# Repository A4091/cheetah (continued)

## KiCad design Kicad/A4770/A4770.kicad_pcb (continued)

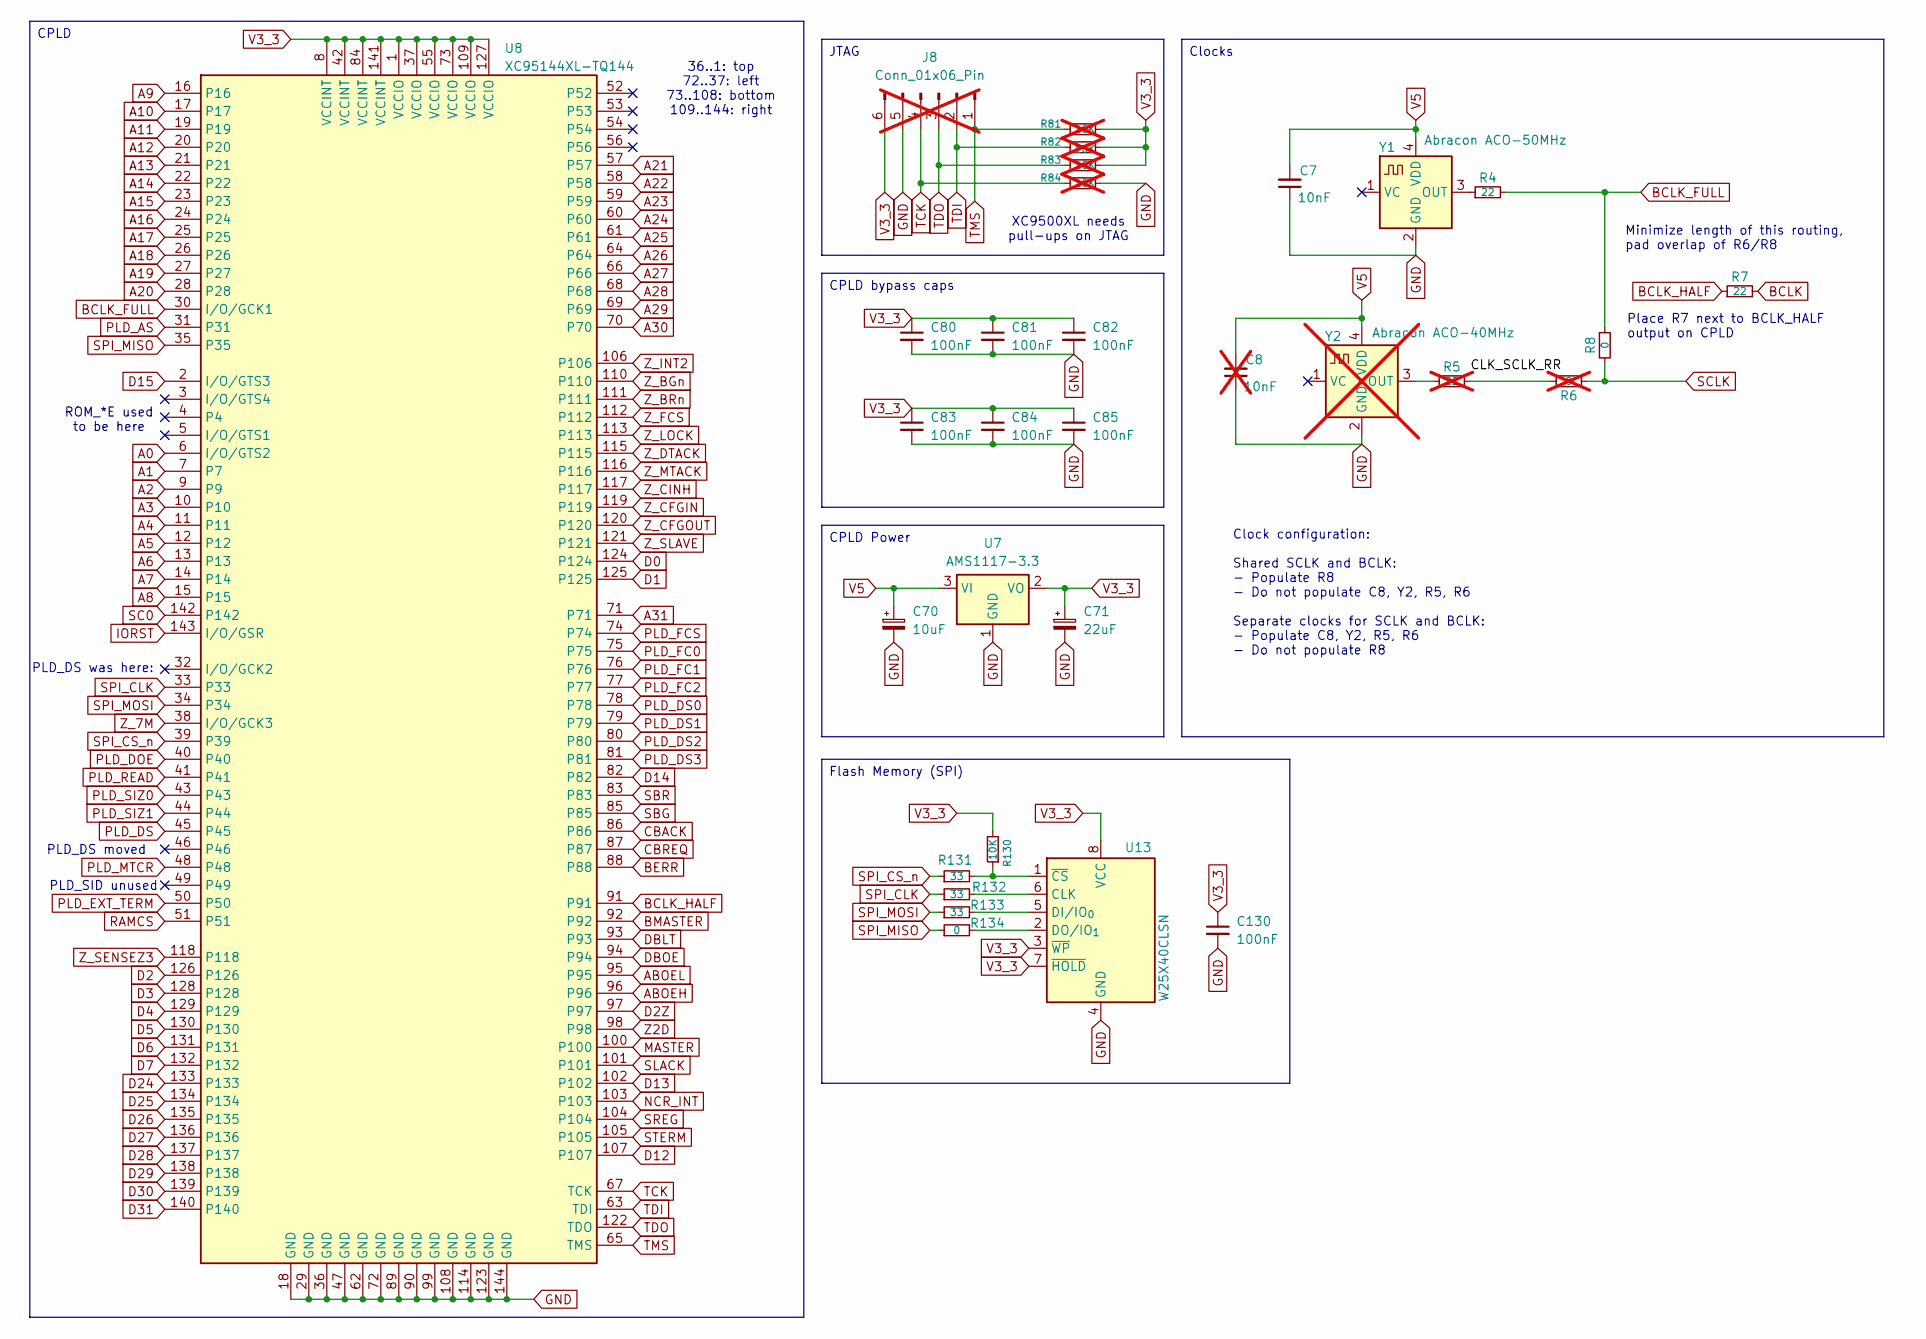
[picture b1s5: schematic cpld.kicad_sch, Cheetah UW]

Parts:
C7: 10nF; C_0603_1608Metric_Pad1.08x0.95mm_HandSolder; LCSC Part # C57112
C8: 10nF; C_0603_1608Metric_Pad1.08x0.95mm_HandSolder; LCSC Part # C57112; not fitted
C70: 10uF; CP_EIA-3528-15_AVX-H_HandSolder; LCSC Part # C7194
C71: 22uF; CP_EIA-3528-15_AVX-H_HandSolder; LCSC Part # C696813
C80, C81, C82, C83, C84, C85, C130: 100nF; C_0603_1608Metric_Pad1.08x0.95mm_HandSolder; LCSC Part # C14663
J8: Conn_01x06_Pin; PinHeader_1x06_P2.54mm_Vertical; LCSC Part # C6332199; not fitted
R4, R7: 22; R_0603_1608Metric; LCSC Part # C23345
R5: 22; R_0603_1608Metric; LCSC Part # C23345; not fitted
R6: 0; R_0603_1608Metric; LCSC Part # C21189; not fitted
R8, R134: 0; R_0603_1608Metric; LCSC Part # C21189
R81, R82, R83, R84: 10K; R_0603_1608Metric_Pad0.98x0.95mm_HandSolder; LCSC Part # C25804; not fitted
R130: 10K; R_0603_1608Metric_Pad0.98x0.95mm_HandSolder; LCSC Part # C25804
R131, R132, R133: 33; R_0603_1608Metric; LCSC Part # C23140
U7: AMS1117-3.3; SOT-223-3_TabPin2; LCSC Part # C6186
U8: XC95144XL-TQ144; TQFP-144_20x20mm_P0.5mm; LCSC Part # C1521137
U13: W25X40CLSN; SOIC-8_multi; LCSC Part # C19617
Y1: Abracon ACO-50MHz; Oscillator_SMD_Fox_FT5H_5.0x3.2mm; LCSC Part # C7431196
Y2: Abracon ACO-40MHz; Oscillator_SMD_Fox_FT5H_5.0x3.2mm; LCSC Part # C7431196; not fitted

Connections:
A0: U8.6 (I/O/GTS2); also elsewhere on the board
A1: U8.7; also elsewhere on the board
A2: U8.9; also elsewhere on the board
A3: U8.10; also elsewhere on the board
A4: U8.11; also elsewhere on the board
A5: U8.12; also elsewhere on the board
A6: U8.13; also elsewhere on the board
A7: U8.14; also elsewhere on the board
A8: U8.15; also elsewhere on the board
A9: U8.16; also elsewhere on the board
A10: U8.17; also elsewhere on the board
A11: U8.19; also elsewhere on the board
A12: U8.20; also elsewhere on the board
A13: U8.21; also elsewhere on the board
A14: U8.22; also elsewhere on the board
A15: U8.23; also elsewhere on the board
A16: U8.24; also elsewhere on the board
A17: U8.25; also elsewhere on the board
A18: U8.26; also elsewhere on the board
A19: U8.27; also elsewhere on the board
A20: U8.28; also elsewhere on the board
A21: U8.57; also elsewhere on the board
A22: U8.58; also elsewhere on the board
A23: U8.59; also elsewhere on the board
A24: U8.60; also elsewhere on the board
A25: U8.61; also elsewhere on the board
A26: U8.64; also elsewhere on the board
A27: U8.66; also elsewhere on the board
A28: U8.68; also elsewhere on the board
A29: U8.69; also elsewhere on the board
A30: U8.70; also elsewhere on the board
A31: U8.71; also elsewhere on the board
ABOEH: U8.96; also elsewhere on the board
ABOEL: U8.95; also elsewhere on the board
BCLK: R7.2; also elsewhere on the board
BCLK_FULL: R4.2, R8.1, U8.30 (I/O/GCK1)
BCLK_HALF: R7.1, U8.91
BERR: U8.88; also elsewhere on the board
BMASTER: U8.92; also elsewhere on the board
CBACK: U8.86; also elsewhere on the board
CBREQ: U8.87; also elsewhere on the board
D0: U8.124; also elsewhere on the board
D1: U8.125; also elsewhere on the board
D2: U8.126; also elsewhere on the board
D2Z: U8.97; also elsewhere on the board
D3: U8.128; also elsewhere on the board
D4: U8.129; also elsewhere on the board
D5: U8.130; also elsewhere on the board
D6: U8.131; also elsewhere on the board
D7: U8.132; also elsewhere on the board
D12: U8.107; also elsewhere on the board
D13: U8.102; also elsewhere on the board
D14: U8.82; also elsewhere on the board
D15: U8.2 (I/O/GTS3); also elsewhere on the board
D24: U8.133; also elsewhere on the board
D25: U8.134; also elsewhere on the board
D26: U8.135; also elsewhere on the board
D27: U8.136; also elsewhere on the board
D28: U8.137; also elsewhere on the board
D29: U8.138; also elsewhere on the board
D30: U8.139; also elsewhere on the board
D31: U8.140; also elsewhere on the board
DBLT: U8.93; also elsewhere on the board
DBOE: U8.94; also elsewhere on the board
GND: C7.1, C8.1, C70.2, C71.2, C80.2, C81.2, C82.2, C83.2, C84.2, C85.2, C130.2, J8.5, R84.1, U7.1 (GND), U8.18 (GND), U8.29 (GND), U8.36 (GND), U8.47 (GND), U8.62 (GND), U8.72 (GND), U8.89 (GND), U8.90 (GND), U8.99 (GND), U8.108 (GND), U8.114 (GND), U8.123 (GND), U8.144 (GND), U13.4 (GND), Y1.2 (GND), Y2.2 (GND); also elsewhere on the board
IORST: U8.143 (I/O/GSR); also elsewhere on the board
MASTER: U8.100; also elsewhere on the board
NCR_INT: U8.103; also elsewhere on the board
unnamed: R5.2, R6.2
unnamed: R132.2, U13.6 (CLK)
unnamed: R133.2, U13.5 (DI/IO_{0})
unnamed: R134.2, U13.2 (DO/IO_{1})
unnamed: R130.1, R131.2, U13.1 (~CS)
unnamed: R4.1, Y1.3 (OUT)
unnamed: R5.1, Y2.3 (OUT)
PLD_AS: U8.31; also elsewhere on the board
PLD_DOE: U8.40; also elsewhere on the board
PLD_DS: U8.45; also elsewhere on the board
PLD_DS0: U8.78; also elsewhere on the board
PLD_DS1: U8.79; also elsewhere on the board
PLD_DS2: U8.80; also elsewhere on the board
PLD_DS3: U8.81; also elsewhere on the board
PLD_EXT_TERM: U8.50; also elsewhere on the board
PLD_FC0: U8.75; also elsewhere on the board
PLD_FC1: U8.76; also elsewhere on the board
PLD_FC2: U8.77; also elsewhere on the board
PLD_FCS: U8.74; also elsewhere on the board
PLD_MTCR: U8.48; also elsewhere on the board
PLD_READ: U8.41; also elsewhere on the board
PLD_SIZ0: U8.43; also elsewhere on the board
PLD_SIZ1: U8.44; also elsewhere on the board
RAMCS: U8.51; also elsewhere on the board
SBG: U8.85; also elsewhere on the board
SBR: U8.83; also elsewhere on the board
SC0: U8.142; also elsewhere on the board
SCLK: R6.1, R8.2; also elsewhere on the board
SLACK: U8.101; also elsewhere on the board
SPI_CLK: R132.1, U8.33
SPI_CS_n: R131.1, U8.39
SPI_MISO: R134.1, U8.35
SPI_MOSI: R133.1, U8.34
SREG: U8.104; also elsewhere on the board
STERM: U8.105; also elsewhere on the board
TCK: J8.4, R84.2, U8.67 (TCK)
TDI: J8.2, R82.2, U8.63 (TDI)
TDO: J8.3, R83.2, U8.122 (TDO)
TMS: J8.1, R81.2, U8.65 (TMS)
V3_3: C71.1, C80.1, C81.1, C82.1, C83.1, C84.1, C85.1, C130.1, J8.6, R81.1, R82.1, R83.1, R130.2, U7.2 (VO), U8.1 (VCCIO), U8.8 (VCCINT), U8.37 (VCCIO), U8.42 (VCCINT), U8.55 (VCCIO), U8.73 (VCCIO), U8.84 (VCCINT), U8.109 (VCCIO), U8.127 (VCCIO), U8.141 (VCCINT), U13.3 (~WP), U13.7 (~HOLD), U13.8 (VCC); also elsewhere on the board
V5: C7.2, C8.2, C70.1, U7.3 (VI), Y1.4 (VDD), Y2.4 (VDD); also elsewhere on the board
Z2D: U8.98; also elsewhere on the board
Z_7M: U8.38 (I/O/GCK3); also elsewhere on the board
Z_BGn: U8.110; also elsewhere on the board
Z_BRn: U8.111; also elsewhere on the board
Z_CFGIN: U8.119; also elsewhere on the board
Z_CFGOUT: U8.120; also elsewhere on the board
Z_CINH: U8.117; also elsewhere on the board
Z_DTACK: U8.115; also elsewhere on the board
Z_FCS: U8.112; also elsewhere on the board
Z_INT2: U8.106; also elsewhere on the board
Z_LOCK: U8.113; also elsewhere on the board
Z_MTACK: U8.116; also elsewhere on the board
Z_SENSEZ3: U8.118; also elsewhere on the board
Z_SLAVE: U8.121; also elsewhere on the board

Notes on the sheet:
Clock configuration: Shared SCLK and BCLK: - Populate R8 - Do not populate C8, Y2, R5, R6 Separate clocks for SCLK and BCLK: - Populate C8, Y2, R5, R6 - Do not populate R8
PLD_SID unused
PLD_DS moved
ROM_*E used to be here
Minimize length of this routing, pad overlap of R6/R8
36..1: top 72..37: left 73..108: bottom 109..144: right
Place R7 next to BCLK_HALF output on CPLD
XC9500XL needs pull-ups on JTAG
PLD_DS was here:
CPLD
Clocks
JTAG
CPLD Power
CPLD bypass caps
Flash Memory (SPI)

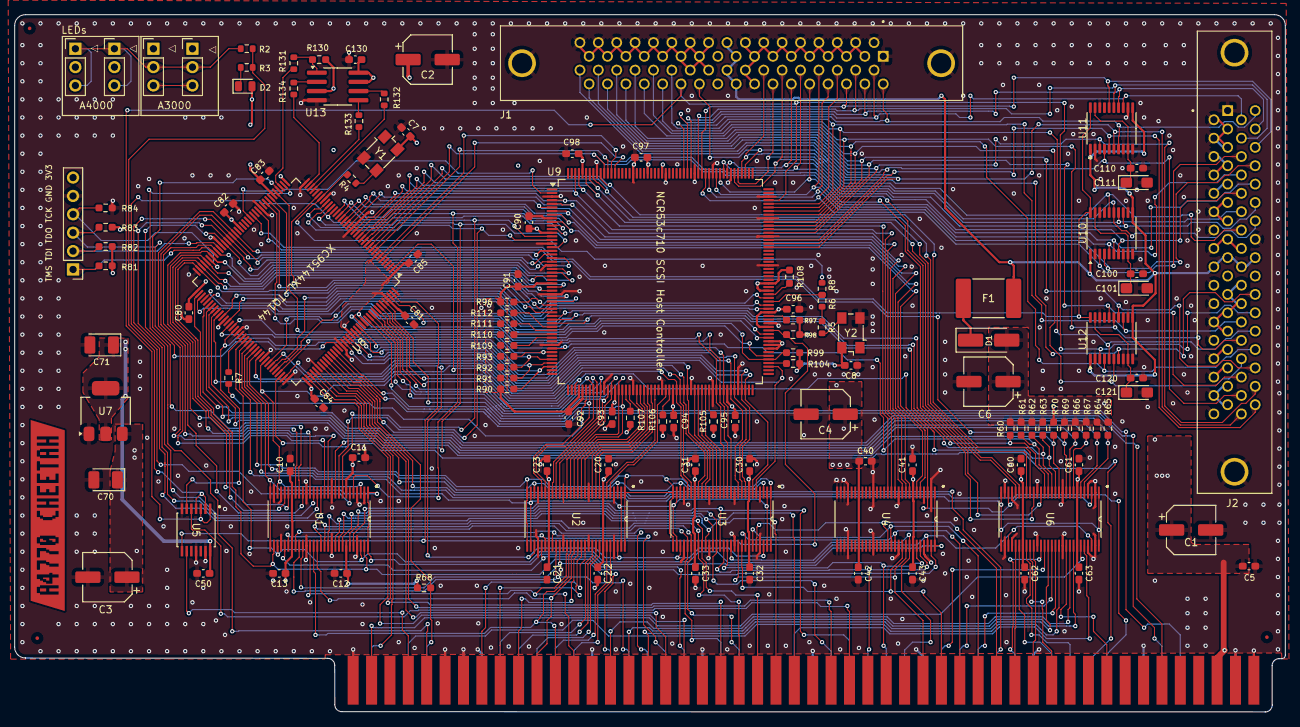
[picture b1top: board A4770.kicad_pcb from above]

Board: 4 copper layers, 175.6 x 96.4 mm, 127 parts (0 on the bottom side), 231 nets.

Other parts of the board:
kibuzzard-696E6D75: G***; kibuzzard-696E6D75

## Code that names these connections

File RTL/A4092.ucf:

# P1 - VCCIO
NET "D<15>"       LOC = "P2";
NET "D<15>"       SLEW = "SLOW";
NET "ROM_CE_n"    LOC = "P3";
NET "ROM_WE_n"    LOC = "P4";
NET "ROM_OE_n"    LOC = "P5";
NET "A<0>"        LOC = "P6";
NET "A<1>"        LOC = "P7";
# P8 - VCCINT
NET "A<2>"        LOC = "P9";
NET "A<3>"        LOC = "P10";
NET "A<4>"        LOC = "P11";
NET "A<5>"        LOC = "P12";
NET "A<6>"        LOC = "P13";
NET "A<7>"        LOC = "P14";
NET "A<8>"        LOC = "P15";
NET "A<9>"        LOC = "P16";
NET "A<10>"       LOC = "P17";
# P18 - GND
NET "A<11>"       LOC = "P19";
NET "A<12>"       LOC = "P20";
NET "A<13>"       LOC = "P21";
NET "A<14>"       LOC = "P22";
NET "A<15>"       LOC = "P23";
NET "A<16>"       LOC = "P24";
NET "A<17>"       LOC = "P25";
NET "A<18>"       LOC = "P26";
NET "A<19>"       LOC = "P27";
NET "A<20>"       LOC = "P28";
# P29 - GND
NET "CLK_50M"     LOC = "P30";
NET "CLK_50M" TNM_NET = "clk";
TIMESPEC "TS_clk" = PERIOD "clk" 20 ns HIGH 50%;
NET "SCSI_AS_n"   LOC = "P31";
NET "SCSI_DS_n"   LOC = "P32";
NET "SPI_CLK"     LOC = "P33";
NET "SPI_MOSI"    LOC = "P34";
NET "SPI_MISO"    LOC = "P35";
# P36 - GND
# P37 - VCCIO
NET "C7M"        LOC = "P38";
NET "C7M" TNM_NET = "C7M";
TIMESPEC "TS_C7M" = PERIOD "C7M" 139.68 ns HIGH 50%;
NET "SPI_CS_n"    LOC = "P39";
NET "DOE"         LOC = "P40";
NET "DOE"         SLEW = "SLOW";
NET "READ"        LOC = "P41";
NET "READ"        SLEW = "SLOW";
# P42 - VCCINT
NET "SIZ<0>"      LOC = "P43";
NET "SIZ<1>"      LOC = "P44";
# P45 - NC
# P46 - NC
# P47 - GND
NET "MTCR_n"      LOC = "P48";
NET "MTCR_n"      SLEW = "SLOW";
NET "SID_n"       LOC = "P49";
NET "DIP_EXT_TERM" LOC = "P50";
# P51 - NC
# P52 - NC
# P53 - NC
# P54 - NC
# P55 - VCCIO
# P56 - NC
# P57 - NC
# P58 - NC
NET "A<23>"       LOC = "P59";
NET "A<24>"       LOC = "P60";
NET "A<25>"       LOC = "P61";
# P62 - GND
# P63 - TDI
NET "A<26>"       LOC = "P64";
# P65 - TMS
NET "A<27>"       LOC = "P66";
# P67 - TCK
NET "A<28>"       LOC = "P68";
NET "A<29>"       LOC = "P69";
NET "A<30>"       LOC = "P70";
NET "A<31>"       LOC = "P71";
# P72 - GND
# P73 - VCCIO
NET "FCS"         LOC = "P74";
NET "FC<0>"       LOC = "P75";
NET "FC<1>"       LOC = "P76";
NET "FC<2>"       LOC = "P77";
NET "DS_n<0>"     LOC = "P78";
NET "DS_n<0>"     SLEW = "SLOW";
NET "DS_n<1>"     LOC = "P79";
NET "DS_n<1>"     SLEW = "SLOW";
NET "DS_n<2>"     LOC = "P80";
NET "DS_n<2>"     SLEW = "SLOW";
NET "DS_n<3>"     LOC = "P81";
NET "DS_n<3>"     SLEW = "SLOW";
NET "D<14>"       LOC = "P82";
NET "D<14>"       SLEW = "SLOW";
NET "SBR_n"       LOC = "P83";
# P84 - VCCINT
NET "SBG_n"       LOC = "P85";
NET "CBACK_n"     LOC = "P86";
NET "CBREQ_n"     LOC = "P87";
NET "BERR_n"      LOC = "P88";
# P89 - GND
# P90 - GND
NET "CLK"         LOC = "P91";
NET "BMASTER"     LOC = "P92";
NET "DBLT"        LOC = "P93";
NET "DBOE_n"      LOC = "P94";
NET "ABOEL_n"     LOC = "P95";
NET "ABOEH_n"     LOC = "P96";
NET "D2Z_n"       LOC = "P97";
NET "Z2D_n"       LOC = "P98";
# P99 - GND
NET "MASTER_n"    LOC = "P100";
NET "SLACK_n"     LOC = "P101";
NET "D<13>"       LOC = "P102";
NET "D<13>"       SLEW = "SLOW";
NET "SINT_n"      LOC = "P103";
NET "SCSI_SREG_n" LOC = "P104";
NET "SCSI_STERM_n" LOC = "P105";
NET "INT2_n"      LOC = "P106";
NET "INT2_n"      SLEW = "SLOW";
NET "D<12>"       LOC = "P107";
NET "D<12>"       SLEW = "SLOW";
# P108 - GND
# P109 - VCCIO
NET "BGn"         LOC = "P110";
NET "BRn"         LOC = "P111";
NET "BRn"         SLEW = "SLOW";
NET "Z_FCS_n"     LOC = "P112";
NET "Z_FCS_n"     SLEW = "SLOW";
NET "Z_LOCK"      LOC = "P113";
# P114 - GND
NET "DTACK_n"     LOC = "P115";
NET "DTACK_n"     SLEW = "SLOW";
NET "MTACK_n"     LOC = "P116";
NET "CINH_n"      LOC = "P117";
NET "CINH_n"      SLEW = "SLOW";
NET "SENSEZ3"     LOC = "P118";
NET "CFGIN_n"     LOC = "P119";
NET "CFGOUT_n"    LOC = "P120";
NET "CFGOUT_n"    SLEW = "SLOW";
NET "SLAVE_n"     LOC = "P121";
NET "SLAVE_n"     SLEW = "SLOW";
# P122 - TDO
# P123 - GND
NET "D<0>"        LOC = "P124";
NET "D<1>"        LOC = "P125";
NET "D<2>"        LOC = "P126";
# P127 - VCCIO
NET "D<3>"        LOC = "P128";
NET "D<4>"        LOC = "P129";
NET "D<5>"        LOC = "P130";
NET "D<6>"        LOC = "P131";
NET "D<7>"        LOC = "P132";
NET "D<24>"       LOC = "P133";
NET "D<25>"       LOC = "P134";
NET "D<26>"       LOC = "P135";
NET "D<27>"       LOC = "P136";
NET "D<28>"       LOC = "P137";
NET "D<28>"       SLEW = "SLOW";
NET "D<29>"       LOC = "P138";
NET "D<29>"       SLEW = "SLOW";
NET "D<30>"       LOC = "P139";
NET "D<30>"       SLEW = "SLOW";
NET "D<31>"       LOC = "P140";
NET "D<31>"       SLEW = "SLOW";
# P141 - VCCINT
NET "SC0"         LOC = "P142";
NET "IORST_n"     LOC = "P143";
NET "IORST_n" TIG;  # Ignore timing on async reset
# P144 - GND

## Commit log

2025-07-14 Fixup address decodes
    *_region was matching when slave_cycle was true but without checking that the base address matched - this would cause these regions to match when other Z3 boards are being accessed
2025-07-14 Fixup DOE
    It must be an inout not an output
    Also add a synchronizer for DOE and DS
2025-07-14 Update README with actual hardware picture and rework document
2025-07-14 Add Schematics for Rev-A and move Production files to REV-A directory
2025-07-14 Update pin setup
    - SENSEZ3_n -> SENSEZ3
    - Adjust SLEW rates (although SLOW is default in Makefile
    - Set unused pins to float for now.
    - Add SC0
2025-07-14 Clean up address handling
    - only the memory map needs all address pins, intreg already uses
    interrupt_region
    - Keep disconnected pins A21/A22 0 for address comparisons or we can't
    match any regions.
2025-07-15 autoconfig does not need inverted BFCS
    But BFCS generation was also wrong.
2025-07-27 a4092flash: Add NVRAM handling code
2025-07-27 Enhanced NVRAM Commands
    The -F option now supports flexible comma-separated combinations:
    Single Operations:
    * a4092flash -F init - Initialize NVRAM partition
    * a4092flash -F osflags - Read os_flags,
    * a4092flash -F switchflags - Read switch_flags,
    * a4092flash -F osflags=ff - Write os_flags,
2025-07-31 KiCAD: Add SCSI Flipper
2025-08-03 a4092flash: Drop 3.3V only parts
2025-08-03 a4092flash: Fix compilation with bebbo's 11.x
2025-08-03 a4092flash: Don't inhibit devices during flashing
    On some lideflash supported devices flash memory and register space
    is shared. Because of that it has to make sure no reads/writes are
    going on while the flashing is in progress.
    On the A4092 however, the host controller registers live separately from
    flash memory.
2025-08-03 a4092flash: Allow flashing of original 4091 ROM
    The original 4091 ROM is only 32KB. So make that the minimum.
2025-08-03 a4092flash: Make gcc happy with SysBase
2025-08-03 a4092flash: make flash bank size configurable
    ... and plumb through bankSize and sectorSize. Also support
    proper handling of 64K sector size.
2025-08-03 a4092flash: Always verify sector erase
2025-08-04 a4092flash: Refactor NVRAM operations
    - Fix printf format specifiers for ULONG addresses using explicit casts
    - Split NVRAM command handling into separate parse and execute phases
    - Add nvramParams structure to store parsed NVRAM operation parameters
    - Move NVRAM execution to after board initialization for proper flash access
    - Replace direct NVRAM_OFFSET usage with board->flashbase + NVRAM_OFFSET
    This improves code organization and ensures NVRAM operations have proper
2025-08-08 Remove a4092flash
    ... because it has been integrated into a4091-software
2025-09-16 Update to latest Verilog
2025-09-19 RTL: Fix whitespace
2025-09-19 RTL: SPI fixes
2025-09-28 Update Schematics and PCB with fixes for known issues
    This commit fixes:
    * U4 enable IORST -> ABOEH
    * U5 VCC 5V -> 3.3V
2025-10-05 Kicad: Add dual footprint for 150mil and 208mil SPI parts
2025-10-05 Add 68pin SCSI connectors
2025-10-05 Add LSI53c770
2025-10-29 First version of A4770 cheetah
2025-10-29 Drop obsolete files
2025-10-29 Drop old files
2025-11-13 Add series resistors for SPI
2025-12-09 Placement updated with latest netlist
2025-12-17 Placement updates -SCSI moved south
2025-12-17 CPLD Placement changes
2025-12-17 Initial routing and signal clean up
2026-01-06 J2 rotated by 180, imported netlist, routing
2026-01-07 Routing
2026-01-09 CPLD Routing
2026-01-09 Fix NCR53C770 footprint
    P119 (Vss) was not in correctly assigned in the footprint.
    Added it, and connected to Vss.
2026-01-09 Mark PLD_SID as NC on U8
    Pin 91 on U8 (PLD_SID) is now unused because there is no
    more DIP switch logic on the board.
2026-01-09 Update PCB from Schematic
2026-01-09 Adjust back side silkscreen on PCB
2026-01-10 Undo last two PCB changes
2026-01-10 Update PCB from Schematic
    (adds series resistors for SPI)
2026-01-10 CPLD Routing WIP
2026-01-10 Undo Update PCB from Schematics
2026-01-10 Series resistor for MISO 33O -> 0O
2026-01-10 U6: Switch from 74ABT16245 to 74ABT16543
    This increases the number of 74ABT16543 parts used and gets rid of the
    74ABT16245 all together, which overall lowers BOM cost despite the 74ABT16245
    being a bit cheaper in single quantities. Given that U6 is also the only part
    we know of that got killed in a Zorro accident pulling the board out of a
    running machine, using a part we are more likely to have spares makes sense.
2026-01-11 Reverse pin order on U6
    the pin lineup changed between 16245 and 16543. Switching the pins around
    will make it easier to reroute to the new chip.
2026-01-11 Fix footprint table to not have hardcoded paths
2026-01-12 Imported netlist and general routing
2026-01-12 U9 data routing
2026-01-14 Clean up pull-up resistors
2026-01-14 General routing
2026-01-18 Fix description and part numbers for SCSI connectors
    Was still using the description for SCSI-2
2026-01-18 Add more clarity around clock circuit
2026-01-18 Tie DIFFSENS to GND not V5
2026-01-18 Revert false change, DIFFSENS -> V5
2026-01-19 Fix up graphics in PCB
2026-01-23 PWR and GND routing
2026-01-24 Rehaul clock circuit in schematics
    and try to add most of the LCSC part numbers
2026-01-24 Rename board from A4092 to A4770
2026-01-25 CLK placement and routing
2026-01-26 U2 placement and routing improvements
2026-01-29 Ruouting completed
2026-01-29 Cleanup
2026-01-30 Board cleanup
2026-01-31 Silkscreen fixes
2026-02-03 J2 rotated by 180 degree, placement and routing updates
2026-02-03 DRCs checks
2026-02-03 Remove SCLK from CPLD
2026-02-05 Imported latest netlist, teardrops, stitching vias, DRCs checks
2026-02-06 Fix issues detected by JLCPCB's uploader
    - Use alternating decoupling caps of 0.01uF and 0.1uF on the
    NCR53c770 as was done on the A4091 design.
    - Remove DNP parts from BOM
    - Remove fiducials from position files.
2026-02-06 Fix footprints
2026-02-07 Remove all unused Library components
    and share fp-lib-table and sym-lib-table between all
    sub projects
2026-02-07 Remove Flipper
    It does not make sense for this design
2026-02-09 Changes from schematics review 26-02-08
2026-02-09 Update RTL to latest 4092 version
2026-02-11 Update TERMPWR diode to DSS34
2026-02-12 Implemented design feedback from final checks
2026-02-15 Fix up part numbers
